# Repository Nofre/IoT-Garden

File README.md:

# IoT-Garden

[Project explained in DevPost](http://devpost.com/software/iot-garden-4x0bi1)

###Dependencies###
* flask
* flask-cors
* pyserial
* Adafruit_BBIO (for BeagleBone)
* Adafruit_DHT (for connect DHTXX sensor to BeagleBone or Raspberry)

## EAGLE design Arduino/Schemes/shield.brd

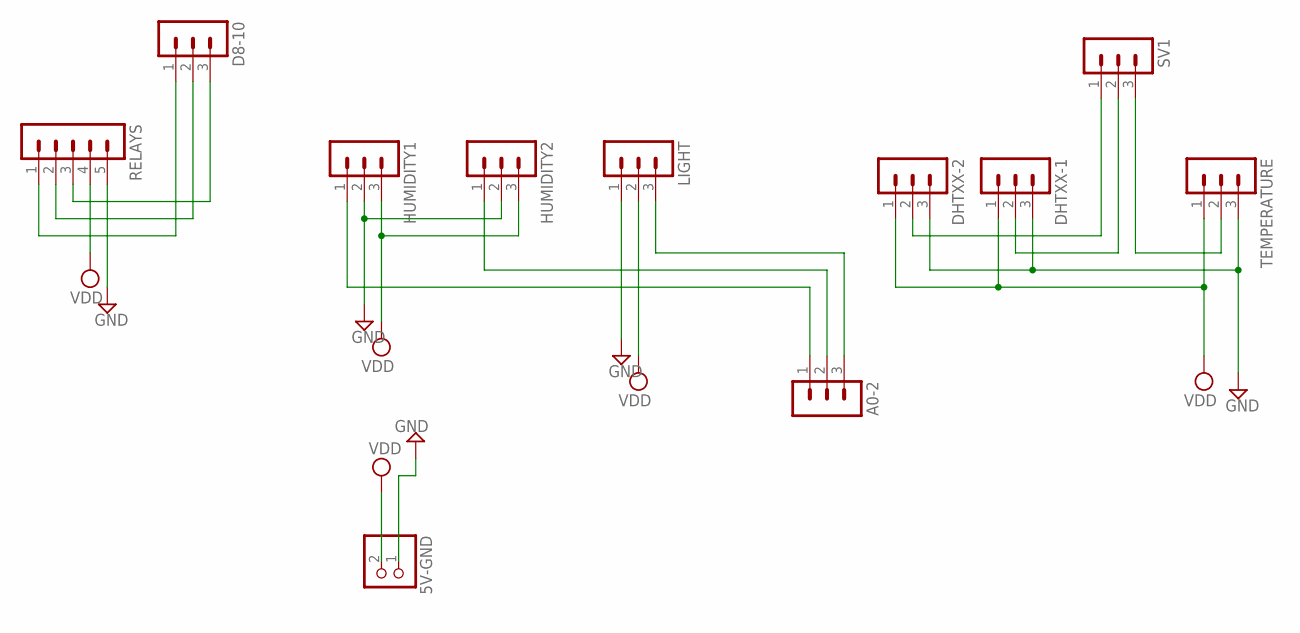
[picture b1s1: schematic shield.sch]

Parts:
5V-GND: PINHD-1X2; 1X02
A0-2: MA03-1
D8-10: MA03-1
DHTXX-1, DHTXX-2: MA03-1
HUMIDITY1, HUMIDITY2: MA03-1
LIGHT: MA03-1
RELAYS: MA05-1
SV1: MA03-1
TEMPERATURE: MA03-1

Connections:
GND: 5V-GND.1, DHTXX-1.3, DHTXX-2.3, HUMIDITY1.2, HUMIDITY2.2, LIGHT.1, RELAYS.5, TEMPERATURE.3
unnamed: DHTXX-1.2, SV1.2
unnamed: SV1.3, TEMPERATURE.2
unnamed: A0-2.1, HUMIDITY1.1
unnamed: D8-10.2, RELAYS.2
unnamed: A0-2.2, HUMIDITY2.1
unnamed: D8-10.1, RELAYS.1
unnamed: A0-2.3, LIGHT.3
unnamed: D8-10.3, RELAYS.3
unnamed: DHTXX-2.2, SV1.1
VDD: 5V-GND.2, DHTXX-1.1, DHTXX-2.1, HUMIDITY1.3, HUMIDITY2.3, LIGHT.2, RELAYS.4, TEMPERATURE.1

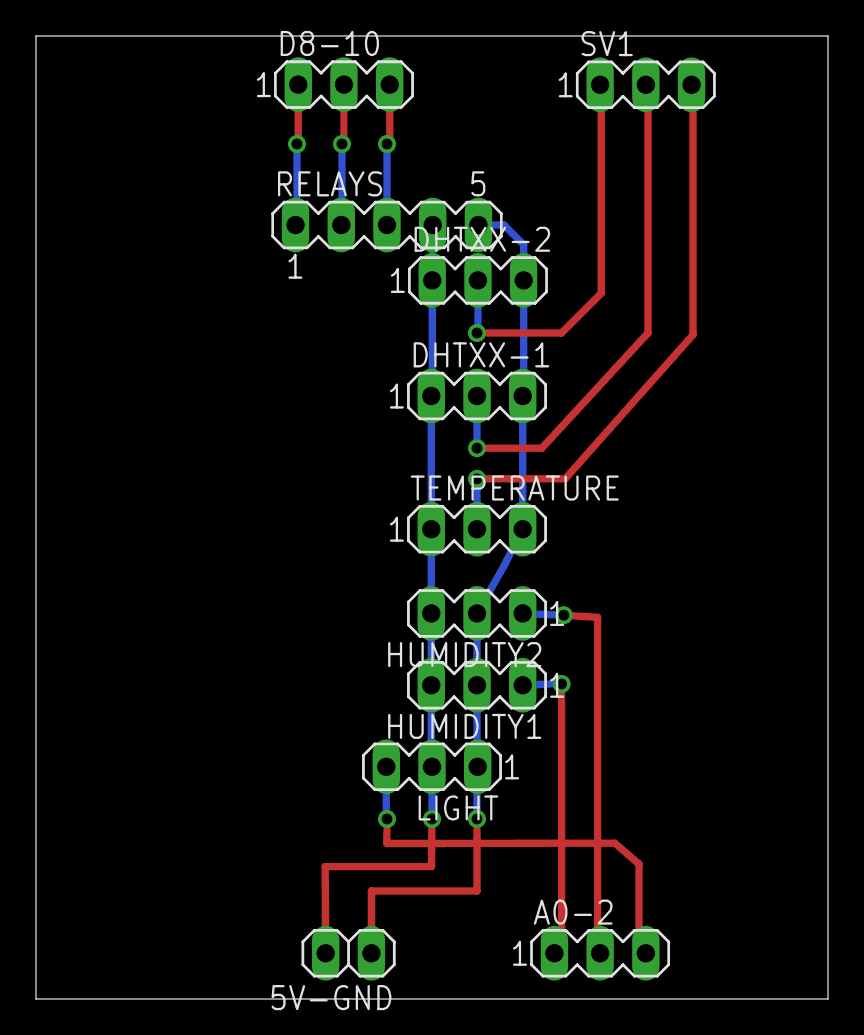
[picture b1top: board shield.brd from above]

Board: 2 copper layers, 44.0 x 53.5 mm, 11 parts (0 on the bottom side), 11 nets.

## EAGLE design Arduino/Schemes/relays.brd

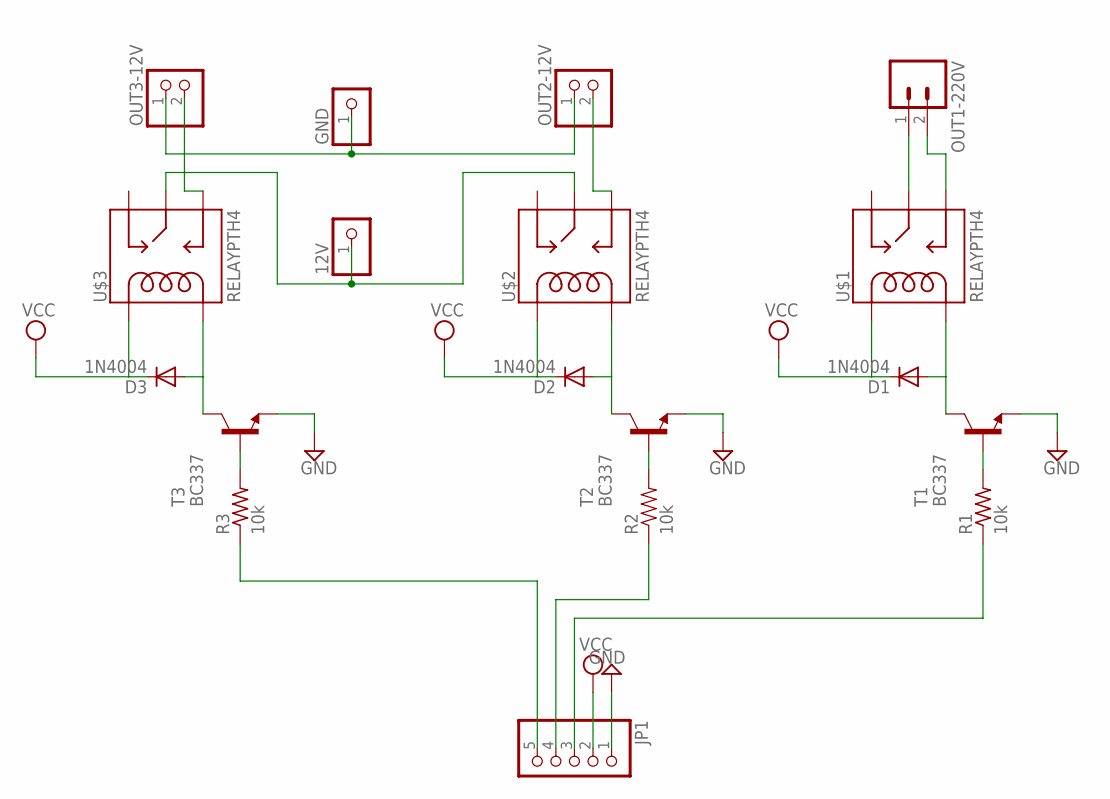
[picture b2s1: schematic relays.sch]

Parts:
12V: PINHD-1X1; 1X01
D1, D2, D3: 1N4004; DO41-10
GND: PINHD-1X1; 1X01
JP1: PINHD-1X5; 1X05
OUT1-220V: M025MM; SCREWTERMINAL-5MM-2
OUT2-12V, OUT3-12V: PINHD-1X2; 1X02
R1, R3: 10k; 0207/15
R2: 10k; AXIAL-0.1
T1, T2, T3: BC337; TO92
U$1, U$2, U$3: RELAYPTH4; RELAY-JZC

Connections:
GND: JP1.1, T1.1 (E), T2.1 (E), T3.1 (E)
unnamed: D3.A, T3.3 (C), U$3.1 (COIL2)
unnamed: OUT1-220V.1, U$1.4 (MAIN)
unnamed: D2.A, T2.3 (C), U$2.1 (COIL2)
unnamed: D1.A, T1.3 (C), U$1.1 (COIL2)
unnamed: R1.2, T1.2 (B)
unnamed: R2.P$2 (2), T2.2 (B)
unnamed: R3.2, T3.2 (B)
unnamed: JP1.3, R1.1
unnamed: JP1.4, R2.P$1 (1)
unnamed: JP1.5, R3.1
unnamed: OUT1-220V.2, U$1.3 (NO)
unnamed: 12V.1, U$2.4 (MAIN), U$3.4 (MAIN)
unnamed: OUT3-12V.2, U$3.3 (NO)
unnamed: OUT2-12V.2, U$2.3 (NO)
unnamed: GND.1, OUT2-12V.1, OUT3-12V.1
VCC: D1.C, D2.C, D3.C, JP1.2, U$1.5 (COIL1), U$2.5 (COIL1), U$3.5 (COIL1)

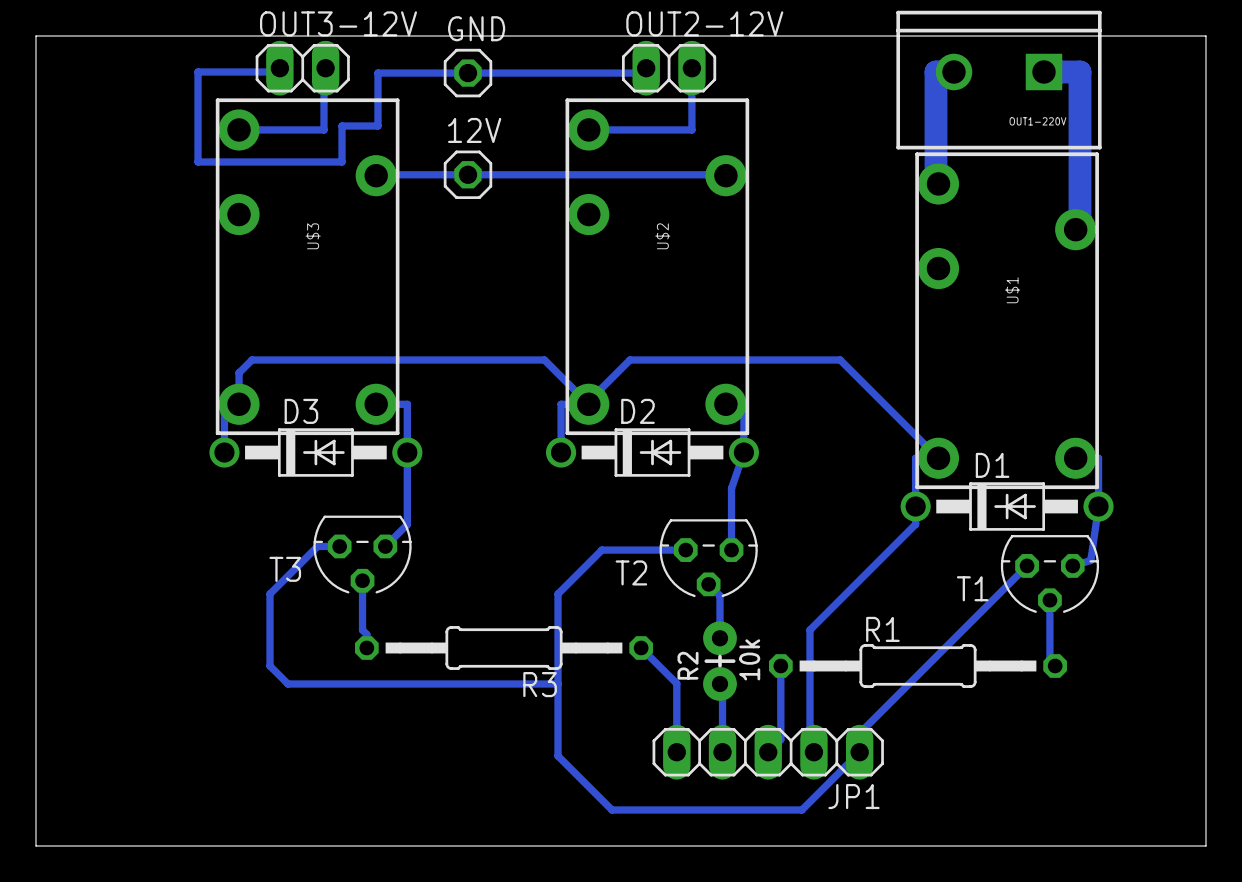
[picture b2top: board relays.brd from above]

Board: 2 copper layers, 65.0 x 45.0 mm, 18 parts (0 on the bottom side), 17 nets.

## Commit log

2016-10-10 First commit, Arduino and MainBoard
2016-10-10 Nodejs server connected to mongodb and angular web app included in the root route
2016-10-10 Modular version. Modified to be compatible with other platforms. NOT TESTED.
2016-10-10 LF line breaks
2016-10-11 argument parser, stubs, bug fixes
2016-10-11 better arduino scheme
2016-10-11 stub prints
2016-10-11 bug fixes
2016-10-14 Arduino shield's scheme, optional sensors
2016-10-14 relay board's scheme, shield with optional DHTxx
2016-10-18 schedule mode, initial status
2016-10-18 RPi DHTXX support, bug fixes, better rest api
2016-10-19 simplified backend and frontend
2016-10-20 web and rest api working
2016-10-21 beagle sc
2016-10-21 bug host
2016-10-21 checkSerial and turn on relays if initial state is ON
2016-10-21 bug serial open
2016-10-26 detects schedule's status when starts
2017-01-22 send date with values
2017-01-22 UI improvements
2017-02-06 schedule in text file

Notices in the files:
parts and their libraries:
SparkFun-Electromechanical: Licensing: Creative Commons ShareAlike 4.0 International - https://creativecommons.org/licenses/by-sa/4.0
